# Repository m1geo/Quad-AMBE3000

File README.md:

# Quad-AMBE3000
A PCB for four DVSI AMBE-3000R (or AMBE-3003) Vocoders for use with WebSDRs/Audio transcoding.

Using four AMBE-3000R parts was cheaper than using a single AMBE-3003, which was the original plan. 
This is useful for VHF, UHF, SHF WebSDR platforms that decode D-Star, DMR, YSF, NXDN, P25, etc.
A soft-codec approach based on [mbelib](https://github.com/szechyjs/mbelib) can be used, but appeared to give poorer decode audio when tested.

Using four AMBE-3003 parts gives a total of 12 similtaneous transcode streams. the '3003 part requires 1V9 instead of 1V8. You may also benefit from increasing the `S_COM_RATE` to 921,600kbps, by changing `S_COM_RATE0` from low to high. See the devices respective datasheets.

The DVSI AMBE parts can be purchased in low volume from the [DVSI Inc. Hardware Product Pricing](https://www.dvsinc.com/products/price.shtml) page. You will need to create a purchase order to buy from DVSI.

# Assembly

The design schematic include details for [JLCPCB](https://jlcpcb.com/) assembly, who assembled mine. You'll likely have to reflow the DVSI AMBE-3000R part yourself, which I did with a PCB reflow hotplate, but you can do any way you wish.

Each schematic component has a [JLCPCB Parts](https://jlcpcb.com/parts)/[LCSC](https://www.lcsc.com/) part number (Cxxxxxx), which can be exported to the BoM using the extra field "LCSC".

# Schematic

[PDF schematic can be found here](outputs/Quad-AMBE3000_Sch.pdf)

# Images

# 3D Renders

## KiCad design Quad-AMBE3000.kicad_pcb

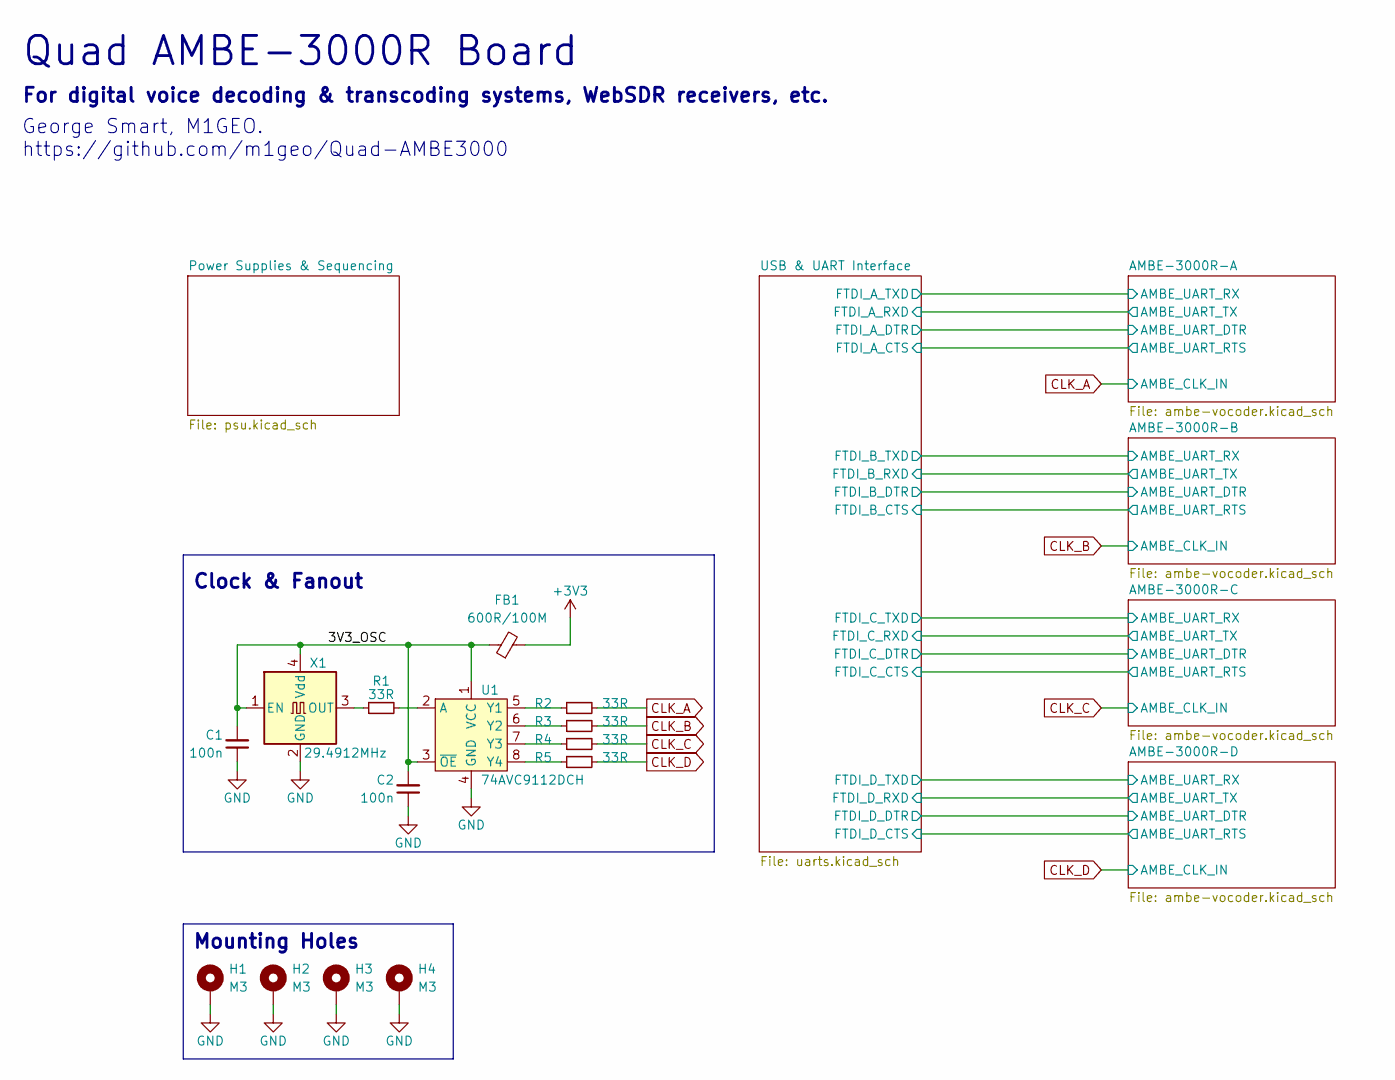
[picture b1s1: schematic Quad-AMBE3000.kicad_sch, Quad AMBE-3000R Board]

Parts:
C1, C2: 100n; C_0603_1608Metric
FB1: 600R/100M; L_0805_2012Metric; LCSC C1017
H1, H2, H3, H4: M3; MountingHole_3.2mm_M3_Pad_Via
R1, R2, R3, R4, R5: 33R; R_0603_1608Metric
U1: 74AVC9112DCH; VSSOP-8_2.4x2.1mm_P0.5mm; LCSC C546283
X1: 29.4912MHz; Oscillator_SMD_Abracon_ASV-4Pin_7.0x5.1mm; LCSC C2901492

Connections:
+3V3: FB1.2; also elsewhere on the board
/3V3_OSC: C1.2, C2.2, FB1.1, U1.1 (VCC), U1.3 (~OE), X1.1 (EN), X1.4 (Vdd)
CLK_A: R2.2; also elsewhere on the board
CLK_B: R3.2; also elsewhere on the board
CLK_C: R4.2; also elsewhere on the board
CLK_D: R5.2; also elsewhere on the board
GND: C1.1, C2.1, H1.1, H2.1, H3.1, H4.1, U1.4 (GND), X1.2 (GND); also elsewhere on the board
unnamed: R1.2, U1.2 (A)
unnamed: R2.1, U1.5 (Y1)
unnamed: R3.1, U1.6 (Y2)
unnamed: R4.1, U1.7 (Y3)
unnamed: R5.1, U1.8 (Y4)
unnamed: R1.1, X1.3 (OUT)

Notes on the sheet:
George Smart, M1GEO. https://github.com/m1geo/Quad-AMBE3000
Quad AMBE-3000R Board
For digital voice decoding & transcoding systems, WebSDR receivers, etc.
Clock & Fanout
Mounting Holes

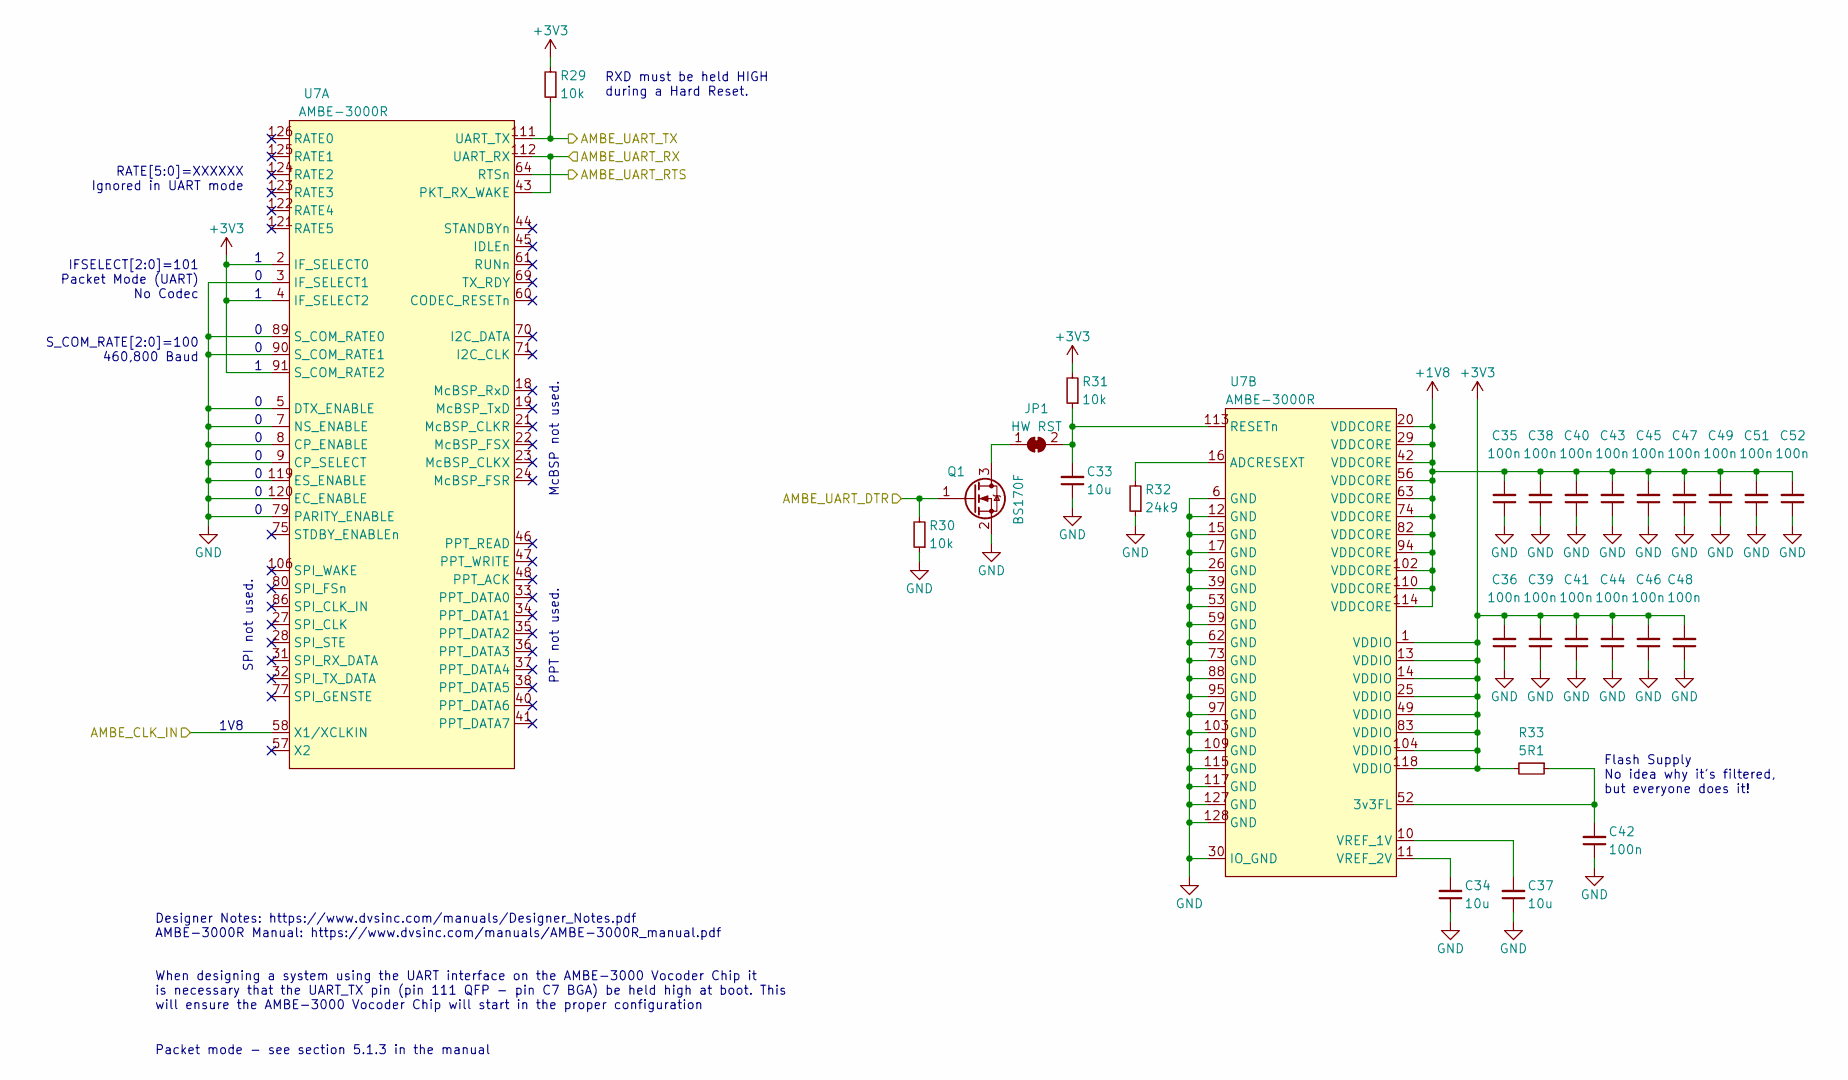
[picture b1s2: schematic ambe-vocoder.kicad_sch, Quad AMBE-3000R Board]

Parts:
C33, C34, C37: 10u; C_0603_1608Metric
C35, C36, C38, C39, C40, C41, C42, C43, C44, C45, C46, C47, C48, C49, C51, C52: 100n; C_0603_1608Metric
JP1: HW RST; SolderJumper-2_P1.3mm_Bridged_RoundedPad1.0x1.5mm
Q1: BS170F; SOT-23
R29, R30, R31: 10k; R_0603_1608Metric
R32: 24k9; R_0603_1608Metric
R33: 5R1; R_0603_1608Metric
U7: AMBE-3000R; LQFP-128_14x14mm_P0.4mm; LCSC DNF

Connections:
+1V8: C35.2, C38.2, C40.2, C43.2, C45.2, C47.2, C49.2, C51.2, C52.2, U7.20 (VDDCORE), U7.29 (VDDCORE), U7.42 (VDDCORE), U7.56 (VDDCORE), U7.63 (VDDCORE), U7.74 (VDDCORE), U7.82 (VDDCORE), U7.94 (VDDCORE), U7.102 (VDDCORE), U7.110 (VDDCORE), U7.114 (VDDCORE); also elsewhere on the board
+3V3: C36.2, C39.2, C41.2, C44.2, C46.2, C48.2, R29.2, R31.2, R33.2, U7.1 (VDDIO), U7.2 (IF_SELECT0), U7.4 (IF_SELECT2), U7.13 (VDDIO), U7.14 (VDDIO), U7.25 (VDDIO), U7.49 (VDDIO), U7.83 (VDDIO), U7.91 (S_COM_RATE2), U7.104 (VDDIO), U7.118 (VDDIO); also elsewhere on the board
/AMBE-3000R-A/AMBE_UART_DTR: Q1.1 (G), R30.2; also elsewhere on the board
/AMBE-3000R-A/AMBE_UART_RTS: U7.64 (RTSn); also elsewhere on the board
/AMBE-3000R-A/AMBE_UART_RX: U7.43 (PKT_RX_WAKE), U7.112 (UART_RX); also elsewhere on the board
/AMBE-3000R-A/AMBE_UART_TX: R29.1, U7.111 (UART_TX); also elsewhere on the board
CLK_A: U7.58 (X1/XCLKIN); also elsewhere on the board
GND: C33.1, C34.1, C35.1, C36.1, C37.1, C38.1, C39.1, C40.1, C41.1, C42.1, C43.1, C44.1, C45.1, C46.1, C47.1, C48.1, C49.1, C51.1, C52.1, Q1.2 (S), R30.1, R32.1, U7.3 (IF_SELECT1), U7.5 (DTX_ENABLE), U7.6 (GND), U7.7 (NS_ENABLE), U7.8 (CP_ENABLE), U7.9 (CP_SELECT), U7.12 (GND), U7.15 (GND), U7.17 (GND), U7.26 (GND), U7.30 (IO_GND), U7.39 (GND), U7.53 (GND), U7.59 (GND), U7.62 (GND), U7.73 (GND), U7.79 (PARITY_ENABLE), U7.88 (GND), U7.89 (S_COM_RATE0), U7.90 (S_COM_RATE1), U7.95 (GND), U7.97 (GND), U7.103 (GND), U7.109 (GND), U7.115 (GND), U7.117 (GND), U7.119 (ES_ENABLE), U7.120 (EC_ENABLE), U7.127 (GND), U7.128 (GND); also elsewhere on the board
unnamed: JP1.1 (A), Q1.3 (D)
unnamed: C33.2, JP1.2 (B), R31.1, U7.113 (RESETn)
unnamed: C42.2, R33.1, U7.52 (3v3FL)
unnamed: R32.2, U7.16 (ADCRESEXT)
unnamed: C37.2, U7.10 (VREF_1V)
unnamed: C34.2, U7.11 (VREF_2V)

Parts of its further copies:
C54, C55, C58, C75, C76, C79, C96, C97, C100: 10u; C_0603_1608Metric
C56, C57, C59, C60, C61, C62, C63, C64, C65, C66, C67, C68, C69, C70, C72, C73, C77, C78, C80, C81, C82, C83, C84, C85, C86, C87, C88, C89, C90, C91, C93, C94, C98, C99, C101, C102, C103, C104, C105, C106, C107, C108, C109, C110, C111, C112, C114, C115: 100n; C_0603_1608Metric
JP2, JP3, JP4: HW RST; SolderJumper-2_P1.3mm_Bridged_RoundedPad1.0x1.5mm
Q2, Q3, Q4: BS170F; SOT-23
R34, R35, R36, R39, R40, R41, R44, R45, R46: 10k; R_0603_1608Metric
R37, R42, R47: 24k9; R_0603_1608Metric
R38, R43, R48: 5R1; R_0603_1608Metric
U8, U9, U10: AMBE-3000R; LQFP-128_14x14mm_P0.4mm; LCSC DNF

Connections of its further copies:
+1V8: C56.2, C59.2, C61.2, C64.2, C66.2, C68.2, C70.2, C72.2, C73.2, C77.2, C80.2, C82.2, C85.2, C87.2, C89.2, C91.2, C93.2, C94.2, C98.2, C101.2, C103.2, C106.2, C108.2, C110.2, C112.2, C114.2, C115.2, U8.20 (VDDCORE), U8.29 (VDDCORE), U8.42 (VDDCORE), U8.56 (VDDCORE), U8.63 (VDDCORE), U8.74 (VDDCORE), U8.82 (VDDCORE), U8.94 (VDDCORE), U8.102 (VDDCORE), U8.110 (VDDCORE), U8.114 (VDDCORE), U9.20 (VDDCORE), U9.29 (VDDCORE), U9.42 (VDDCORE), U9.56 (VDDCORE), U9.63 (VDDCORE), U9.74 (VDDCORE), U9.82 (VDDCORE), U9.94 (VDDCORE), U9.102 (VDDCORE), U9.110 (VDDCORE), U9.114 (VDDCORE), U10.20 (VDDCORE), U10.29 (VDDCORE), U10.42 (VDDCORE), U10.56 (VDDCORE), U10.63 (VDDCORE), U10.74 (VDDCORE), U10.82 (VDDCORE), U10.94 (VDDCORE), U10.102 (VDDCORE), U10.110 (VDDCORE), U10.114 (VDDCORE); also elsewhere on the board
+3V3: C57.2, C60.2, C62.2, C65.2, C67.2, C69.2, C78.2, C81.2, C83.2, C86.2, C88.2, C90.2, C99.2, C102.2, C104.2, C107.2, C109.2, C111.2, R34.2, R36.2, R38.2, R39.2, R41.2, R43.2, R44.2, R46.2, R48.2, U8.1 (VDDIO), U8.2 (IF_SELECT0), U8.4 (IF_SELECT2), U8.13 (VDDIO), U8.14 (VDDIO), U8.25 (VDDIO), U8.49 (VDDIO), U8.83 (VDDIO), U8.91 (S_COM_RATE2), U8.104 (VDDIO), U8.118 (VDDIO), U9.1 (VDDIO), U9.2 (IF_SELECT0), U9.4 (IF_SELECT2), U9.13 (VDDIO), U9.14 (VDDIO), U9.25 (VDDIO), U9.49 (VDDIO), U9.83 (VDDIO), U9.91 (S_COM_RATE2), U9.104 (VDDIO), U9.118 (VDDIO), U10.1 (VDDIO), U10.2 (IF_SELECT0), U10.4 (IF_SELECT2), U10.13 (VDDIO), U10.14 (VDDIO), U10.25 (VDDIO), U10.49 (VDDIO), U10.83 (VDDIO), U10.91 (S_COM_RATE2), U10.104 (VDDIO), U10.118 (VDDIO); also elsewhere on the board
/AMBE-3000R-B/AMBE_UART_DTR: Q2.1 (G), R35.2; also elsewhere on the board
/AMBE-3000R-B/AMBE_UART_RTS: U8.64 (RTSn); also elsewhere on the board
/AMBE-3000R-B/AMBE_UART_RX: U8.43 (PKT_RX_WAKE), U8.112 (UART_RX); also elsewhere on the board
/AMBE-3000R-B/AMBE_UART_TX: R34.1, U8.111 (UART_TX); also elsewhere on the board
/AMBE-3000R-C/AMBE_UART_DTR: Q3.1 (G), R40.2; also elsewhere on the board
/AMBE-3000R-C/AMBE_UART_RTS: U9.64 (RTSn); also elsewhere on the board
/AMBE-3000R-C/AMBE_UART_RX: U9.43 (PKT_RX_WAKE), U9.112 (UART_RX); also elsewhere on the board
/AMBE-3000R-C/AMBE_UART_TX: R39.1, U9.111 (UART_TX); also elsewhere on the board
/AMBE-3000R-D/AMBE_UART_DTR: Q4.1 (G), R45.2; also elsewhere on the board
/AMBE-3000R-D/AMBE_UART_RTS: U10.64 (RTSn); also elsewhere on the board
/AMBE-3000R-D/AMBE_UART_RX: U10.43 (PKT_RX_WAKE), U10.112 (UART_RX); also elsewhere on the board
/AMBE-3000R-D/AMBE_UART_TX: R44.1, U10.111 (UART_TX); also elsewhere on the board
CLK_B: U8.58 (X1/XCLKIN); also elsewhere on the board
CLK_C: U9.58 (X1/XCLKIN); also elsewhere on the board
CLK_D: U10.58 (X1/XCLKIN); also elsewhere on the board
GND: C54.1, C55.1, C56.1, C57.1, C58.1, C59.1, C60.1, C61.1, C62.1, C63.1, C64.1, C65.1, C66.1, C67.1, C68.1, C69.1, C70.1, C72.1, C73.1, C75.1, C76.1, C77.1, C78.1, C79.1, C80.1, C81.1, C82.1, C83.1, C84.1, C85.1, C86.1, C87.1, C88.1, C89.1, C90.1, C91.1, C93.1, C94.1, C96.1, C97.1, C98.1, C99.1, C100.1, C101.1, C102.1, C103.1, C104.1, C105.1, C106.1, C107.1, C108.1, C109.1, C110.1, C111.1, C112.1, C114.1, C115.1, Q2.2 (S), Q3.2 (S), Q4.2 (S), R35.1, R37.1, R40.1, R42.1, R45.1, R47.1, U8.3 (IF_SELECT1), U8.5 (DTX_ENABLE), U8.6 (GND), U8.7 (NS_ENABLE), U8.8 (CP_ENABLE), U8.9 (CP_SELECT), U8.12 (GND), U8.15 (GND), U8.17 (GND), U8.26 (GND), U8.30 (IO_GND), U8.39 (GND), U8.53 (GND), U8.59 (GND), U8.62 (GND), U8.73 (GND), U8.79 (PARITY_ENABLE), U8.88 (GND), U8.89 (S_COM_RATE0), U8.90 (S_COM_RATE1), U8.95 (GND), U8.97 (GND), U8.103 (GND), U8.109 (GND), U8.115 (GND), U8.117 (GND), U8.119 (ES_ENABLE), U8.120 (EC_ENABLE), U8.127 (GND), U8.128 (GND), U9.3 (IF_SELECT1), U9.5 (DTX_ENABLE), U9.6 (GND), U9.7 (NS_ENABLE), U9.8 (CP_ENABLE), U9.9 (CP_SELECT), U9.12 (GND), U9.15 (GND), U9.17 (GND), U9.26 (GND), U9.30 (IO_GND), U9.39 (GND), U9.53 (GND), U9.59 (GND), U9.62 (GND), U9.73 (GND), U9.79 (PARITY_ENABLE), U9.88 (GND), U9.89 (S_COM_RATE0), U9.90 (S_COM_RATE1), U9.95 (GND), U9.97 (GND), U9.103 (GND), U9.109 (GND), U9.115 (GND), U9.117 (GND), U9.119 (ES_ENABLE), U9.120 (EC_ENABLE), U9.127 (GND), U9.128 (GND), U10.3 (IF_SELECT1), U10.5 (DTX_ENABLE), U10.6 (GND), U10.7 (NS_ENABLE), U10.8 (CP_ENABLE), U10.9 (CP_SELECT), U10.12 (GND), U10.15 (GND), U10.17 (GND), U10.26 (GND), U10.30 (IO_GND), U10.39 (GND), U10.53 (GND), U10.59 (GND), U10.62 (GND), U10.73 (GND), U10.79 (PARITY_ENABLE), U10.88 (GND), U10.89 (S_COM_RATE0), U10.90 (S_COM_RATE1), U10.95 (GND), U10.97 (GND), U10.103 (GND), U10.109 (GND), U10.115 (GND), U10.117 (GND), U10.119 (ES_ENABLE), U10.120 (EC_ENABLE), U10.127 (GND), U10.128 (GND); also elsewhere on the board
unnamed: JP2.1 (A), Q2.3 (D)
unnamed: C54.2, JP2.2 (B), R36.1, U8.113 (RESETn)
unnamed: JP3.1 (A), Q3.3 (D)
unnamed: C75.2, JP3.2 (B), R41.1, U9.113 (RESETn)
unnamed: JP4.1 (A), Q4.3 (D)
unnamed: C96.2, JP4.2 (B), R46.1, U10.113 (RESETn)
unnamed: C63.2, R38.1, U8.52 (3v3FL)
unnamed: R37.2, U8.16 (ADCRESEXT)
unnamed: C58.2, U8.10 (VREF_1V)
unnamed: C55.2, U8.11 (VREF_2V)
unnamed: C84.2, R43.1, U9.52 (3v3FL)
unnamed: R42.2, U9.16 (ADCRESEXT)
unnamed: C79.2, U9.10 (VREF_1V)
unnamed: C76.2, U9.11 (VREF_2V)
unnamed: C105.2, R48.1, U10.52 (3v3FL)
unnamed: R47.2, U10.16 (ADCRESEXT)
unnamed: C100.2, U10.10 (VREF_1V)
unnamed: C97.2, U10.11 (VREF_2V)

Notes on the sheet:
1V8
IFSELECT[2:0]=101 Packet Mode (UART) No Codec
McBSP not used.
RATE[5:0]=XXXXXX Ignored in UART mode
Packet mode - see section 5.1.3 in the manual
Designer Notes: https://www.dvsinc.com/manuals/Designer_Notes.pdf AMBE-3000R Manual: https://www.dvsinc.com/manuals/AMBE-3000R_manual.pdf
S_COM_RATE[2:0]=100 460,800 Baud
PPT not used.
Flash Supply No idea why it's filtered, but everyone does it!
SPI not used.
RXD must be held HIGH during a Hard Reset.
When designing a system using the UART interface on the AMBE-3000 Vocoder Chip it is necessary that the UART_TX pin (pin 111 QFP - pin C7 BGA) be held high at boot. This will ensure the AMBE-3000 Vocoder Chip will start in the proper configuration

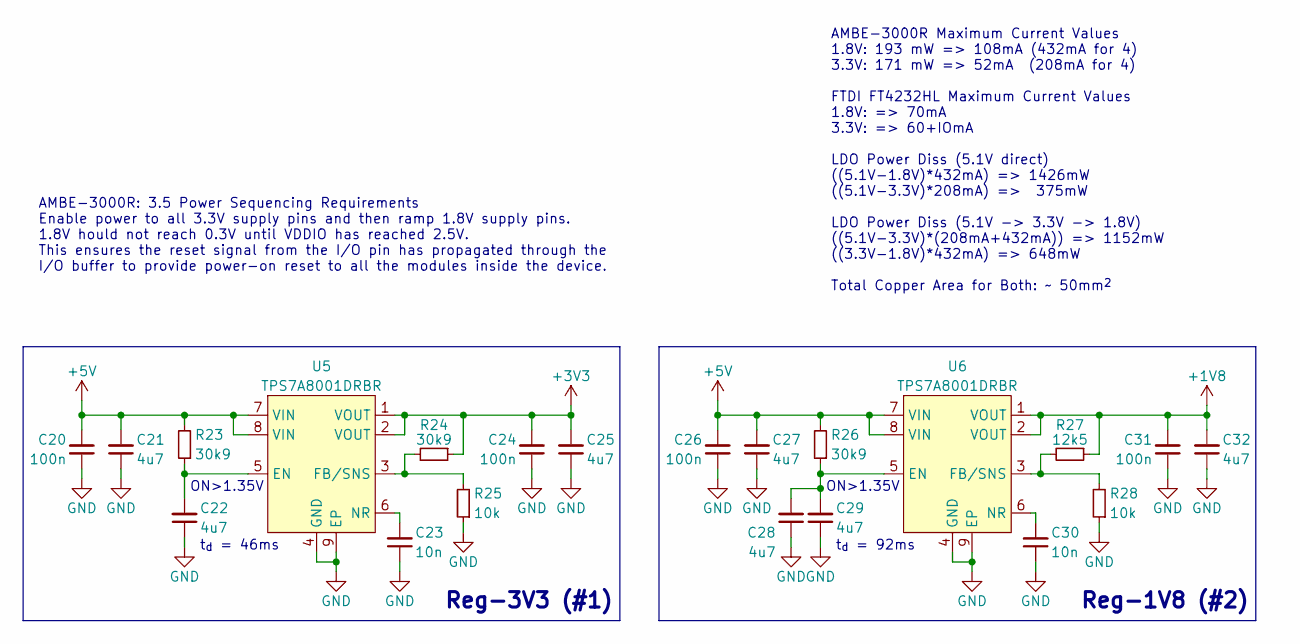
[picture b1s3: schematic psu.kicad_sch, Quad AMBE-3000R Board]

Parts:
C20, C24, C26, C31: 100n; C_0603_1608Metric
C21, C22, C25, C27, C28, C29, C32: 4u7; C_0603_1608Metric
C23, C30: 10n; C_0603_1608Metric
R23, R24, R26: 30k9; R_0603_1608Metric
R25, R28: 10k; R_0603_1608Metric
R27: 12k5; R_0603_1608Metric
U5, U6: TPS7A8001DRBR; Texas_DRB0008A; LCSC C105265

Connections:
+1V8: C31.2, C32.2, R27.1, U6.1 (VOUT), U6.2 (VOUT); also elsewhere on the board
+3V3: C24.2, C25.2, R24.1, U5.1 (VOUT), U5.2 (VOUT); also elsewhere on the board
+5V: C20.2, C21.2, C26.2, C27.2, R23.2, R26.2, U5.7 (VIN), U5.8 (VIN), U6.7 (VIN), U6.8 (VIN); also elsewhere on the board
GND: C20.1, C21.1, C22.1, C23.1, C24.1, C25.1, C26.1, C27.1, C28.1, C29.1, C30.1, C31.1, C32.1, R25.1, R28.1, U5.4 (GND), U5.9 (EP), U6.4 (GND), U6.9 (EP); also elsewhere on the board
unnamed: C22.2, R23.1, U5.5 (EN)
unnamed: R24.2, R25.2, U5.3 (FB/SNS)
unnamed: C23.2, U5.6 (NR)
unnamed: C28.2, C29.2, R26.1, U6.5 (EN)
unnamed: R27.2, R28.2, U6.3 (FB/SNS)
unnamed: C30.2, U6.6 (NR)

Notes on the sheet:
AMBE-3000R: 3.5 Power Sequencing Requirements Enable power to all 3.3V supply pins and then ramp 1.8V supply pins. 1.8V hould not reach 0.3V until VDDIO has reached 2.5V. This ensures the reset signal from the I/O pin has propagated through the I/O buffer to provide power-on reset to all the module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
AMBE-3000R Maximum Current Values 1.8V: 193 mW => 108mA (432mA for 4) 3.3V: 171 mW => 52mA (208mA for 4) FTDI FT4232HL Maximum Current Values 1.8V: => 70mA 3.3V: => 60+IOmA LDO Power Diss (5.1V direct) ((5.1V-1.8V)*432mA) => 1426mW ((5.1V-3.3V)*208mA) => 375mW LDO Power Diss (5.1V -> 3.3V -> 1.8V) 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
Reg-3V3 (#1)
Reg-1V8 (#2)
t_{d} = 46ms
ON>1.35V
t_{d} = 92ms

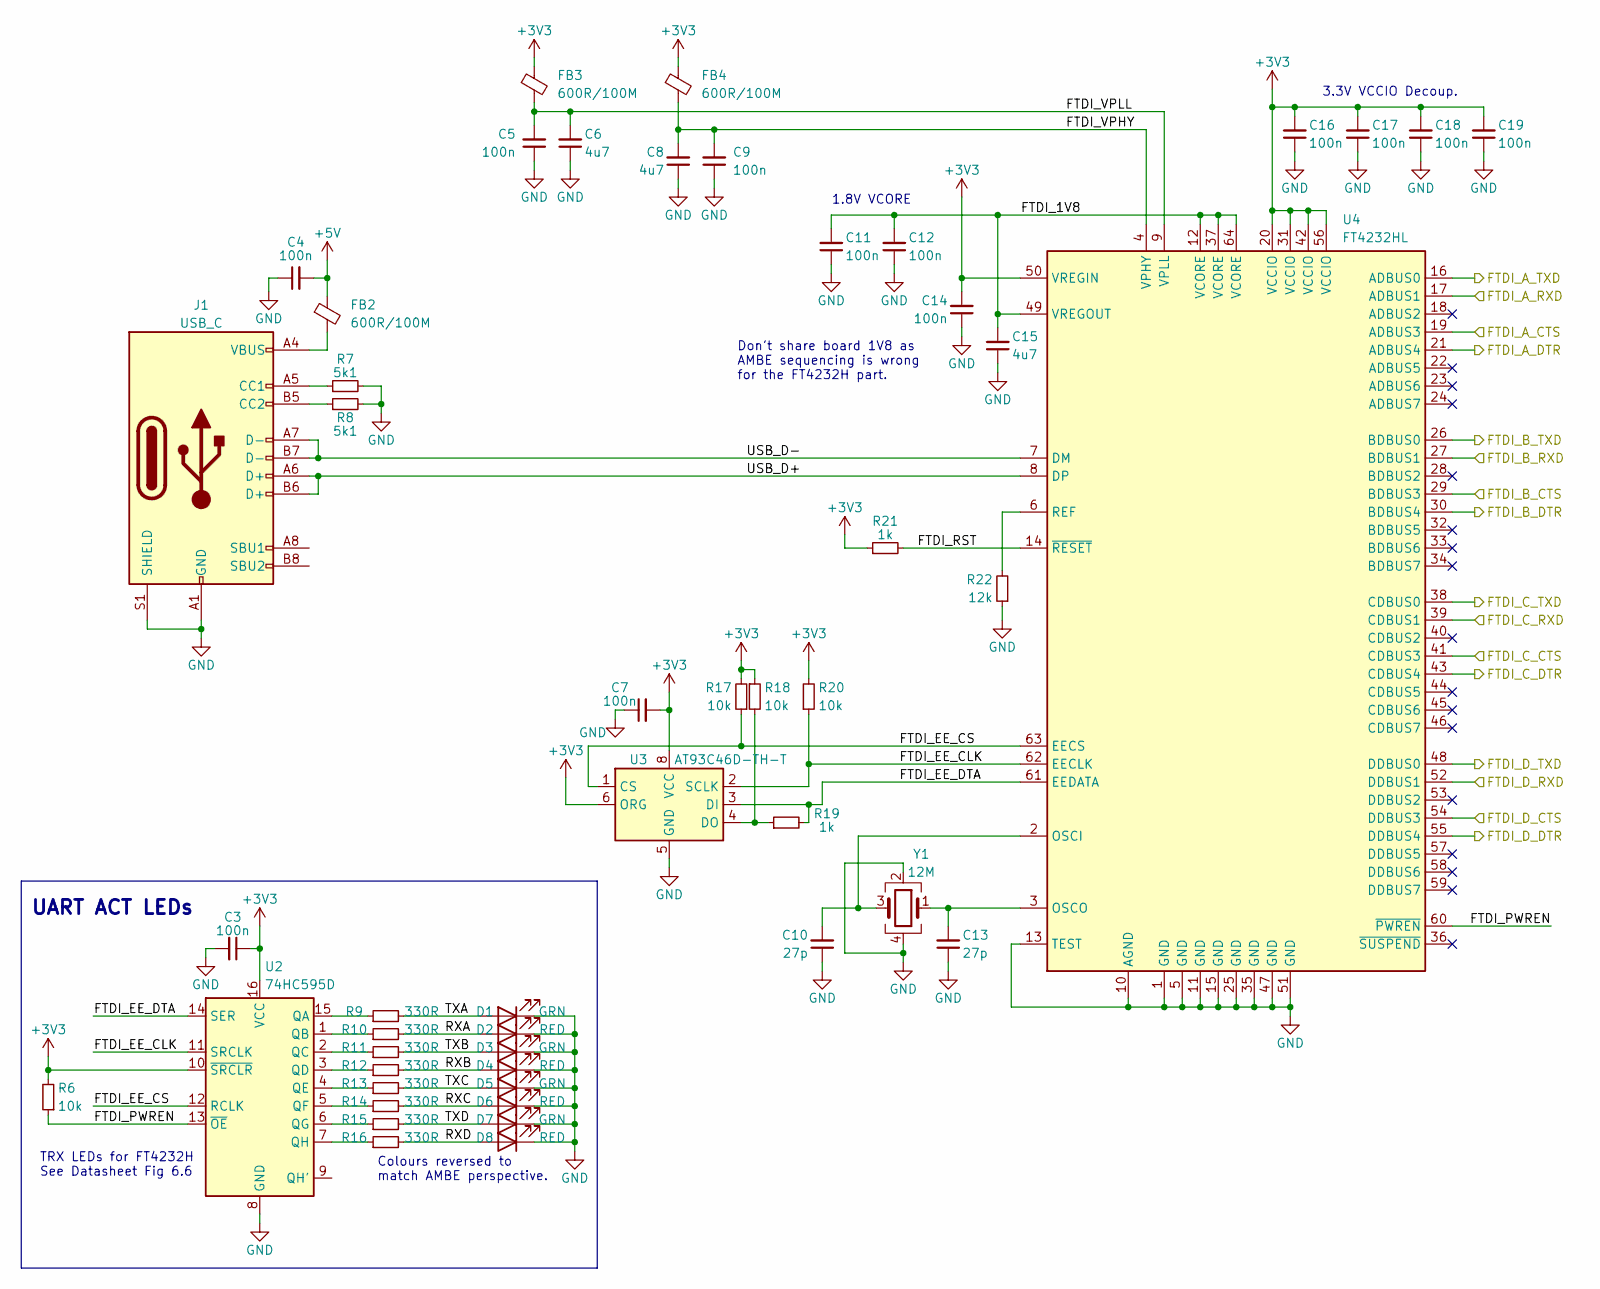
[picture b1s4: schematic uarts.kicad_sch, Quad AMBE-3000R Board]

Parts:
C3, C4, C5, C7, C9, C11, C12, C14, C16, C17, C18, C19: 100n; C_0603_1608Metric
C6, C8, C15: 4u7; C_0603_1608Metric
C10, C13: 27p; C_0603_1608Metric
D1, D3, D5, D7: GRN; LED_0603_1608Metric
D2, D4, D6, D8: RED; LED_0603_1608Metric
FB2, FB3, FB4: 600R/100M; L_0805_2012Metric; LCSC C1017
J1: USB_C; USB_C_Receptacle_GCT_USB4110; LCSC C963217
R6, R17, R18, R20: 10k; R_0603_1608Metric
R7, R8: 5k1; R_0603_1608Metric
R9, R10, R11, R12, R13, R14, R15, R16: 330R; R_0603_1608Metric
R19, R21: 1k; R_0603_1608Metric
R22: 12k; R_0603_1608Metric
U2: 74HC595D; SO-16_3.9x9.9mm_P1.27mm; LCSC C5947
U3: AT93C46D-TH-T; TSSOP-8_4.4x3mm_P0.65mm; LCSC C2061936
U4: FT4232HL; LQFP-64_10x10mm_P0.5mm; LCSC C56742
Y1: 12M; Crystal_SMD_3225-4Pin_3.2x2.5mm; LCSC C362340

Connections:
+3V3: C3.1, C7.2, C14.2, C16.2, C17.2, C18.2, C19.2, FB3.1, FB4.1, R6.2, R17.2, R18.1, R20.2, R21.1, U2.10 (~SRCLR), U2.16 (VCC), U3.6 (ORG), U3.8 (VCC), U4.20 (VCCIO), U4.31 (VCCIO), U4.42 (VCCIO), U4.50 (VREGIN), U4.56 (VCCIO); also elsewhere on the board
+5V: C4.2, FB2.1; also elsewhere on the board
/AMBE-3000R-A/AMBE_UART_DTR: U4.21 (ADBUS4); also elsewhere on the board
/AMBE-3000R-A/AMBE_UART_RTS: U4.19 (ADBUS3); also elsewhere on the board
/AMBE-3000R-A/AMBE_UART_RX: U4.16 (ADBUS0); also elsewhere on the board
/AMBE-3000R-A/AMBE_UART_TX: U4.17 (ADBUS1); also elsewhere on the board
/AMBE-3000R-B/AMBE_UART_DTR: U4.30 (BDBUS4); also elsewhere on the board
/AMBE-3000R-B/AMBE_UART_RTS: U4.29 (BDBUS3); also elsewhere on the board
/AMBE-3000R-B/AMBE_UART_RX: U4.26 (BDBUS0); also elsewhere on the board
/AMBE-3000R-B/AMBE_UART_TX: U4.27 (BDBUS1); also elsewhere on the board
/AMBE-3000R-C/AMBE_UART_DTR: U4.43 (CDBUS4); also elsewhere on the board
/AMBE-3000R-C/AMBE_UART_RTS: U4.41 (CDBUS3); also elsewhere on the board
/AMBE-3000R-C/AMBE_UART_RX: U4.38 (CDBUS0); also elsewhere on the board
/AMBE-3000R-C/AMBE_UART_TX: U4.39 (CDBUS1); also elsewhere on the board
/AMBE-3000R-D/AMBE_UART_DTR: U4.55 (DDBUS4); also elsewhere on the board
/AMBE-3000R-D/AMBE_UART_RTS: U4.54 (DDBUS3); also elsewhere on the board
/AMBE-3000R-D/AMBE_UART_RX: U4.48 (DDBUS0); also elsewhere on the board
/AMBE-3000R-D/AMBE_UART_TX: U4.52 (DDBUS1); also elsewhere on the board
/USB & UART Interface/FTDI_1V8: C11.2, C12.2, C15.2, U4.12 (VCORE), U4.37 (VCORE), U4.49 (VREGOUT), U4.64 (VCORE)
/USB & UART Interface/FTDI_EE_CLK: R20.1, U2.11 (SRCLK), U3.2 (SCLK), U4.62 (EECLK)
/USB & UART Interface/FTDI_EE_CS: R17.1, U2.12 (RCLK), U3.1 (CS), U4.63 (EECS)
/USB & UART Interface/FTDI_EE_DTA: R19.2, U2.14 (SER), U3.3 (DI), U4.61 (EEDATA)
/USB & UART Interface/FTDI_PWREN: R6.1, U2.13 (~OE), U4.60 (~PWREN)
/USB & UART Interface/FTDI_RST: R21.2, U4.14 (~RESET)
/USB & UART Interface/FTDI_VPHY: C8.2, C9.2, FB4.2, U4.4 (VPHY)
/USB & UART Interface/FTDI_VPLL: C5.2, C6.2, FB3.2, U4.9 (VPLL)
/USB & UART Interface/RXA: D2.2 (A), R10.2
/USB & UART Interface/RXB: D4.2 (A), R12.2
/USB & UART Interface/RXC: D6.2 (A), R14.2
/USB & UART Interface/RXD: D8.2 (A), R16.2
/USB & UART Interface/TXA: D1.2 (A), R9.2
/USB & UART Interface/TXB: D3.2 (A), R11.2
/USB & UART Interface/TXC: D5.2 (A), R13.2
/USB & UART Interface/TXD: D7.2 (A), R15.2
/USB & UART Interface/USB_D+: J1.A6 (D+), J1.B6 (D+), U4.8 (DP)
/USB & UART Interface/USB_D-: J1.A7 (D-), J1.B7 (D-), U4.7 (DM)
GND: C3.2, C4.1, C5.1, C6.1, C7.1, C8.1, C9.1, C10.1, C11.1, C12.1, C13.1, C14.1, C15.1, C16.1, C17.1, C18.1, C19.1, D1.1 (K), D2.1 (K), D3.1 (K), D4.1 (K), D5.1 (K), D6.1 (K), D7.1 (K), D8.1 (K), J1.A1 (GND), J1.A12 (GND), J1.B1 (GND), J1.B12 (GND), J1.S1 (SHIELD), R7.2, R8.2, R22.1, U2.8 (GND), U3.5 (GND), U4.1 (GND), U4.5 (GND), U4.10 (AGND), U4.11 (GND), U4.13 (TEST), U4.15 (GND), U4.25 (GND), U4.35 (GND), U4.47 (GND), U4.51 (GND), Y1.2, Y1.4; also elsewhere on the board
unnamed: FB2.2, J1.A4 (VBUS), J1.A9 (VBUS), J1.B4 (VBUS), J1.B9 (VBUS)
unnamed: J1.A5 (CC1), R7.1
unnamed: J1.B5 (CC2), R8.1
unnamed: R9.1, U2.15 (QA)
unnamed: R10.1, U2.1 (QB)
unnamed: R11.1, U2.2 (QC)
unnamed: R12.1, U2.3 (QD)
unnamed: R13.1, U2.4 (QE)
unnamed: R14.1, U2.5 (QF)
unnamed: R15.1, U2.6 (QG)
unnamed: R16.1, U2.7 (QH)
unnamed: R18.2, R19.1, U3.4 (DO)
unnamed: C10.2, U4.2 (OSCI), Y1.3
unnamed: C13.2, U4.3 (OSCO), Y1.1
unnamed: R22.2, U4.6 (REF)

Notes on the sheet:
Colours reversed to match AMBE perspective.
UART ACT LEDs
TRX LEDs for FT4232H See Datasheet Fig 6.6
1.8V VCORE
3.3V VCCIO Decoup.
Don't share board 1V8 as AMBE sequencing is wrong for the FT4232H part.

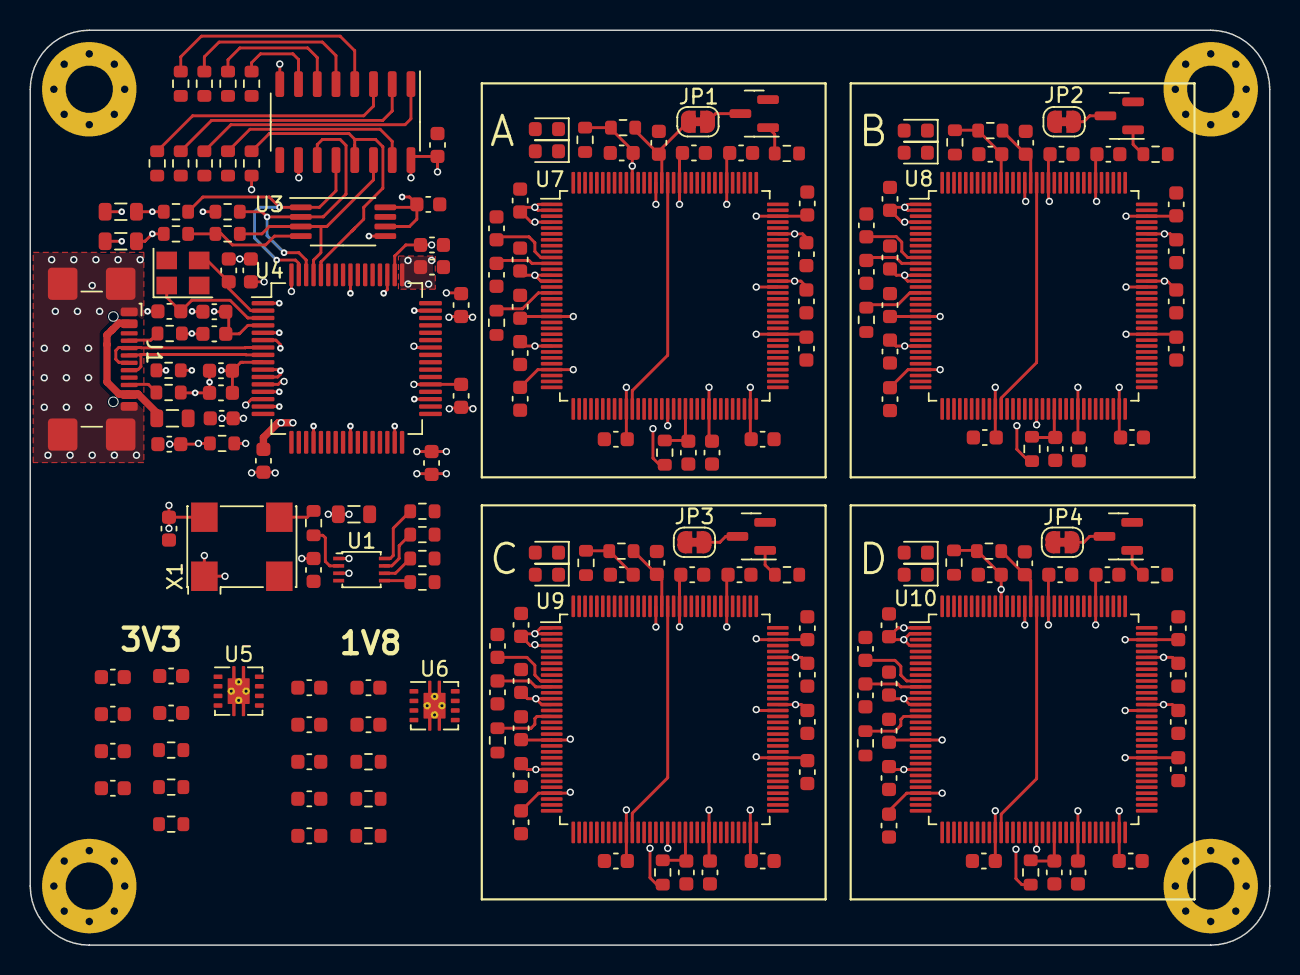
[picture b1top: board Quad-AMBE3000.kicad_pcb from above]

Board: 4 copper layers, 84.0 x 62.0 mm, 193 parts (0 on the bottom side), 94 nets.

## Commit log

2024-02-20 Initial files for Quad AMBE-3000R PCB
2024-02-21 UARTS & PSU finished. Just AMBE-3000R stuff to go
2024-02-23 Added the AMBE-3000F
2024-02-23 Schematic V1 done
2024-02-25 Most of the layout done
2024-02-26 Routing finished. Need to tidy DRC & BoM
2024-02-26 Finished DRC review. Warnings for silkscreen overlap with artwork on back side.
2024-02-26 Final updates before manufacture of V1.00
2024-02-26 Added images to updated readme
2024-02-27 Fixed USB C BoM option.
2024-03-07 Changed Y1 part information from 24MHz to 12MHz
2024-03-11 Added some images of the final board.
2024-03-12 Updated README typo
2024-03-12 Added construction notes
2024-03-12 Fixed readme
